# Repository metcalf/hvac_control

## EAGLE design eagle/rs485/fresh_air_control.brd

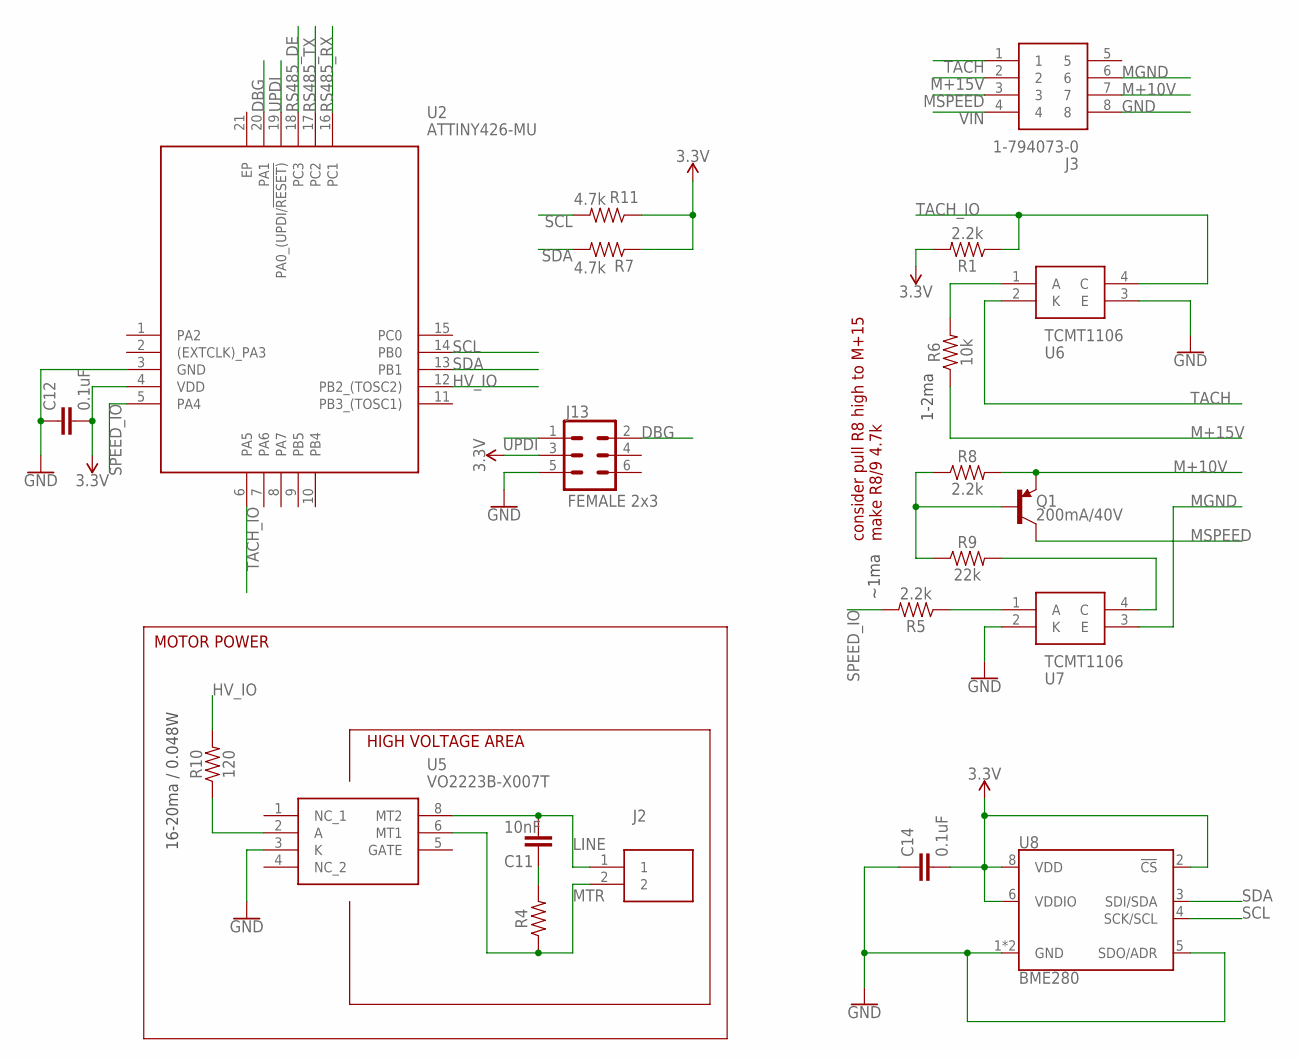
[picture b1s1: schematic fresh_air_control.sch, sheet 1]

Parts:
C11: 10nF; 0805
C12, C14: 0.1uF; 0603
J2: 1-770166-0; 17701660
J3: 1-794073-0; 17940730
J13: FEMALE 2x3; 2X3
Q1: 200mA/40V; SOT23-3
R1, R5, R8: 2.2k; 0603
R4: 100; 0805
R6: 10k; 0603
R7, R11: 4.7k; 0603
R9: 22k; 0603
R10: 120; 0603
U2: ATTINY426-MU; QFN40P300X300X90-21N
U5: VO2223B-X007T; VO2223BX007T
U6, U7: TCMT1106; SOIC127P700X230-4N
U8: BME280; LGA-8-2.5X2.5

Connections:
3.3V: C12.2, C14.2, J13.3, R1.2, R7.1, R11.1, U2.4 (VDD), U8.2 (!CS), U8.6 (VDDIO), U8.8 (VDD); also elsewhere on the board
DBG: J13.2, U2.20 (PA1)
GND: C12.1, C14.1, J3.8, J13.5, U2.3 (GND), U5.3 (K), U6.3 (E), U7.2 (K), U8.1 (GND), U8.5 (SDO/ADR), U8.7 (GND); also elsewhere on the board
HV_IO: R10.2, U2.12 (PB2_(TOSC2)); also elsewhere on the board
HV_SW: R10.1, U5.2 (A)
LINE: C11.1, J2.1, U5.8 (MT2)
M+10V: J3.7, Q1.2 (E), R8.2
M+15V: J3.2, R6.1
MGND: J3.6, U7.3 (E)
MSPEED: J3.3, Q1.3 (C)
MTR: J2.2, R4.1, U5.6 (MT1)
unnamed: R6.2, U6.1 (A)
unnamed: C11.2, R4.2
unnamed: R5.1, U7.1 (A)
unnamed: Q1.1 (B), R8.1, R9.1
unnamed: R9.2, U7.4 (C)
RS485_DE: U2.18 (PC3); also elsewhere on the board
RS485_RX: U2.16 (PC1); also elsewhere on the board
RS485_TX: U2.17 (PC2); also elsewhere on the board
SCL: R11.2, U2.14 (PB0), U8.4 (SCK/SCL); also elsewhere on the board
SDA: R7.2, U2.13 (PB1), U8.3 (SDI/SDA); also elsewhere on the board
SPEED_IO: R5.2, U2.5 (PA4); also elsewhere on the board
TACH: J3.1, U6.2 (K)
TACH_IO: R1.1, U2.6 (PA5), U6.4 (C); also elsewhere on the board
UPDI: J13.1, U2.19 (PA0_(UPDI/!RESET))
VIN: J3.4; also elsewhere on the board

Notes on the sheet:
HIGH VOLTAGE AREA
16-20ma / 0.048W
~1ma
1-2ma
MOTOR POWER
consider pull R8 high to M+15 make R8/9 4.7k

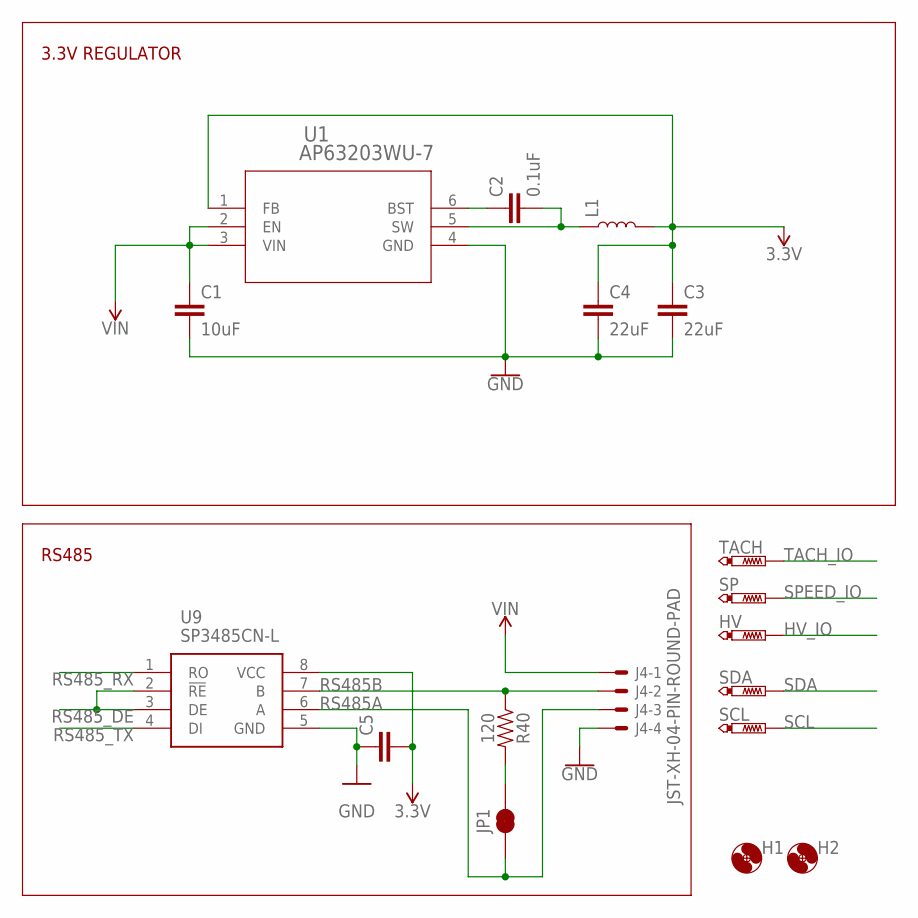
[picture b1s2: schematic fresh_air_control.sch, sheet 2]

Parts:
C1: 10uF; 1206
C2, C5: 0.1uF; 0603
C3, C4: 22uF; 0805
H1, H2: MOUNT-HOLE3.3; 3,3
HV: PTR1B1,27; B1,27
J4: JST-XH-04-PIN-ROUND-PAD; JST-XH-04-PACKAGE-ROUND-PAD
JP1: JUMPER-SMT_2_NC_TRACE_NO-SILK; SMT-JUMPER_2_NC_TRACE_NO-SILK
L1: 4.7μH_SHIELDED_INDUCTOR; 1008(2520)
R40: 120; 0603
SCL: PTR1B1,27; B1,27
SDA: PTR1B1,27; B1,27
SP: PTR1B1,27; B1,27
TACH: PTR1B1,27; B1,27
U1: AP63203WU-7; SOIC_05WU-7_DIO
U9: SP3485CN-L; SOIC127P600X175-8N

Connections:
3.3V: C3.1, C4.1, C5.2, L1.2, U1.1 (FB), U9.8 (VCC); also elsewhere on the board
GND: C1.2, C3.2, C4.2, C5.1, J4.4, U1.4 (GND), U9.5 (GND); also elsewhere on the board
HV_IO: HV.TP; also elsewhere on the board
unnamed: C2.2, L1.1, U1.5 (SW)
unnamed: C2.1, U1.6 (BST)
unnamed: JP1.2, R40.2
RS485A: J4.3, JP1.1, U9.6 (A)
RS485B: J4.2, R40.1, U9.7 (B)
RS485_DE: U9.2 (!RE), U9.3 (DE); also elsewhere on the board
RS485_RX: U9.1 (RO); also elsewhere on the board
RS485_TX: U9.4 (DI); also elsewhere on the board
SCL: SCL.TP; also elsewhere on the board
SDA: SDA.TP; also elsewhere on the board
SPEED_IO: SP.TP; also elsewhere on the board
TACH_IO: TACH.TP; also elsewhere on the board
VIN: C1.1, J4.1, U1.2 (EN), U1.3 (VIN); also elsewhere on the board

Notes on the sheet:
3.3V REGULATOR
RS485

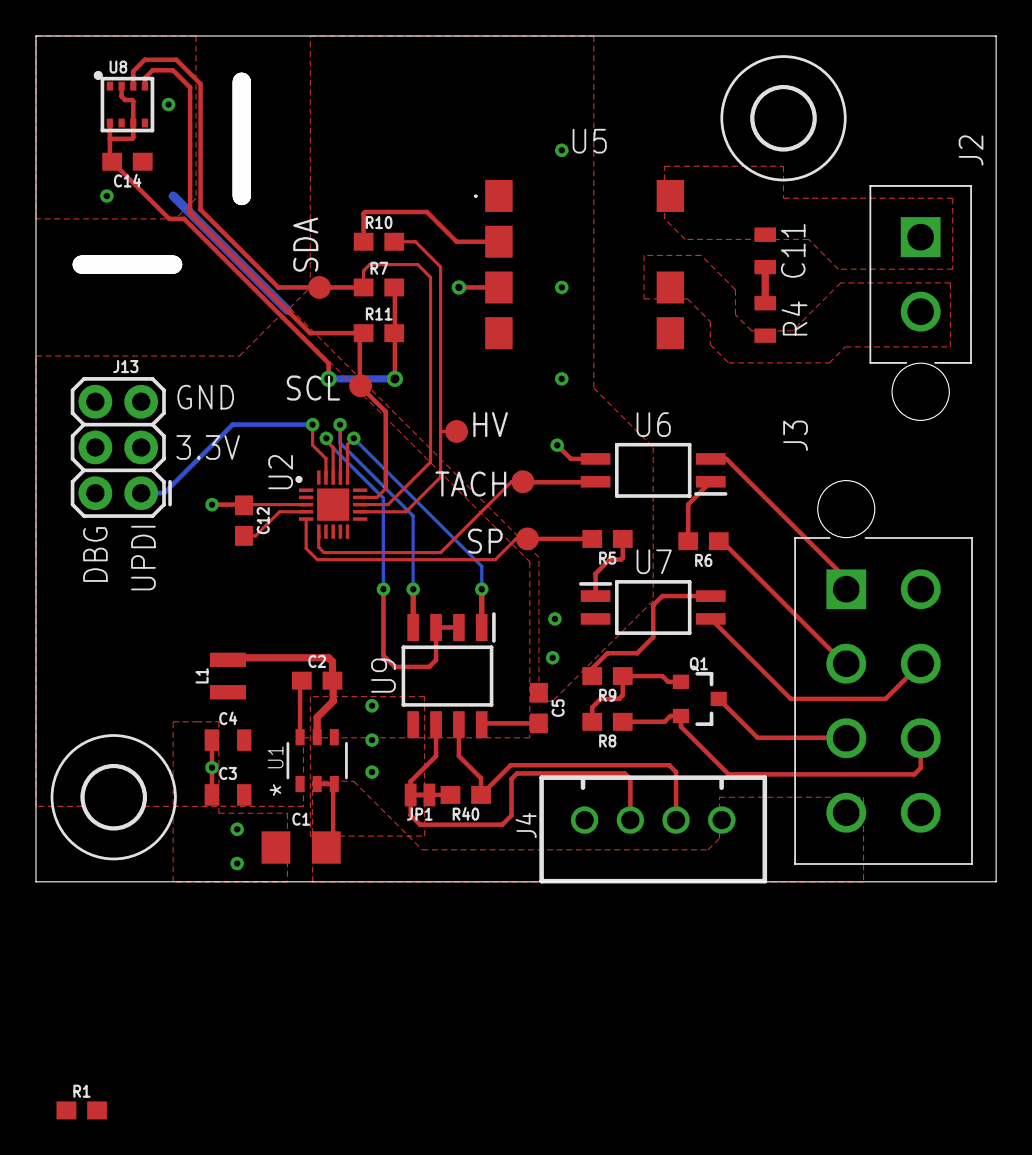
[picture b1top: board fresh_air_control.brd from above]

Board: 2 copper layers, 53.3 x 47.0 mm, 39 parts (0 on the bottom side), 31 nets.

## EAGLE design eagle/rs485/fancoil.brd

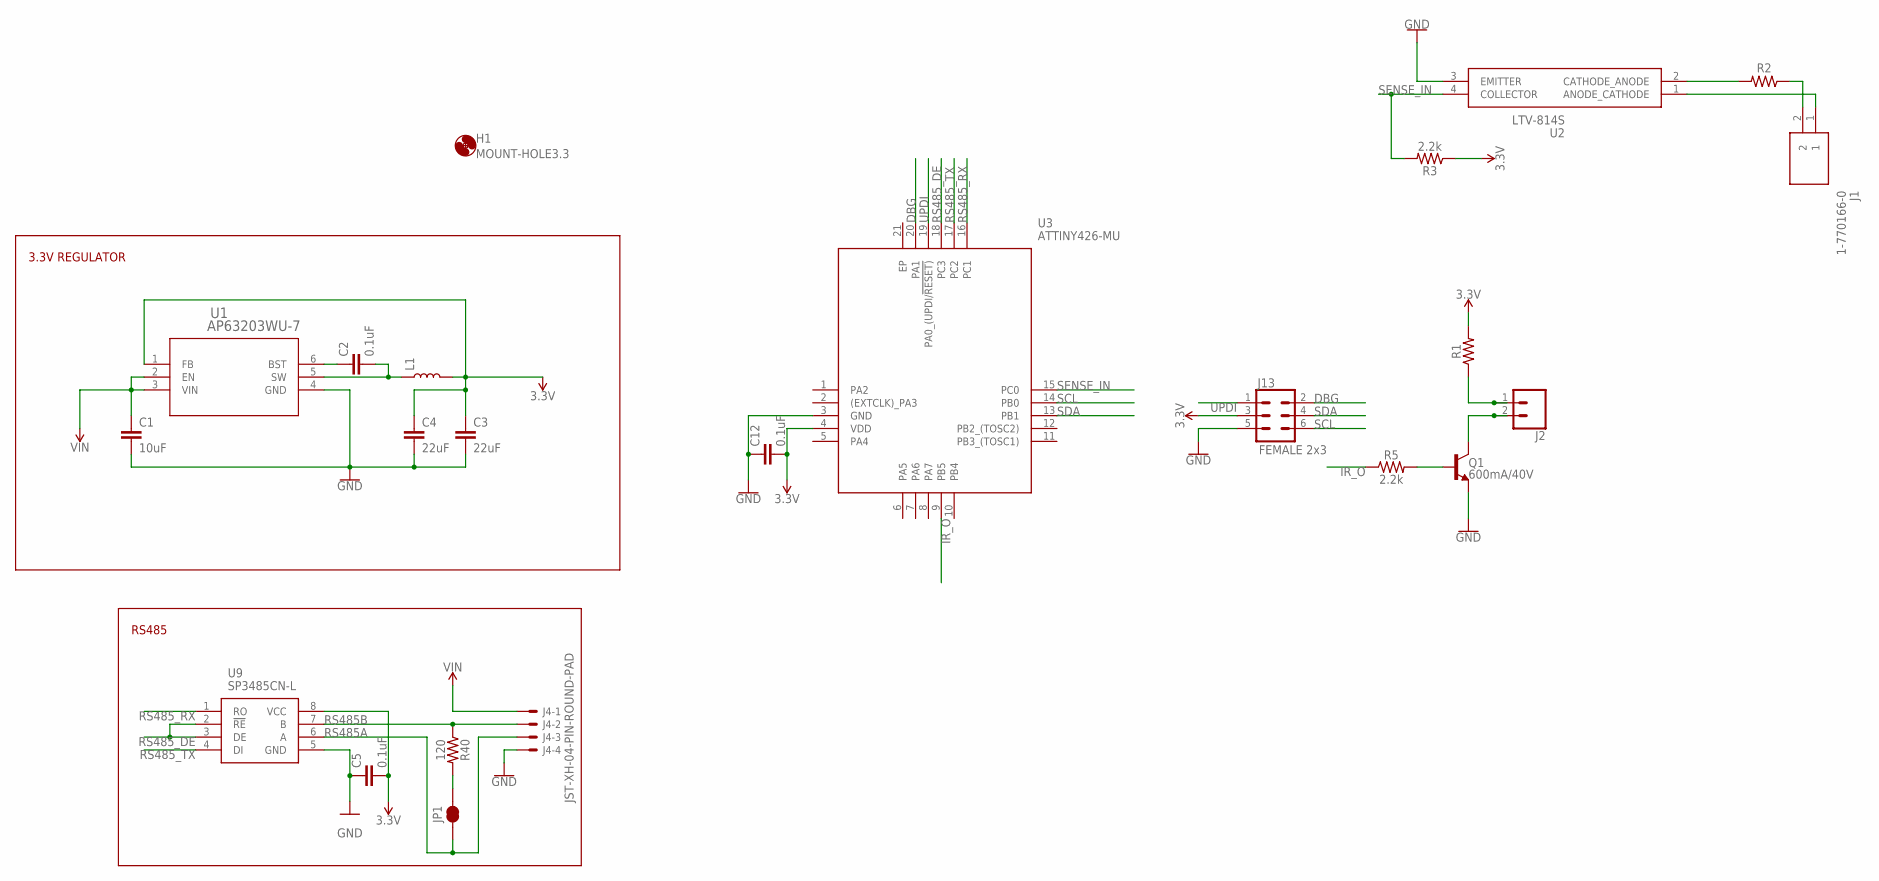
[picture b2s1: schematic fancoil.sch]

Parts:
C1: 10uF; 1206
C2, C5, C12: 0.1uF; 0603
C3, C4: 22uF; 0805
H1: MOUNT-HOLE3.3; 3,3
J1: 1-770166-0; 17701660
J2: CONN_02; 1X02
J4: JST-XH-04-PIN-ROUND-PAD; JST-XH-04-PACKAGE-ROUND-PAD
J13: FEMALE 2x3; 2X3
JP1: JUMPER-SMT_2_NC_TRACE_NO-SILK; SMT-JUMPER_2_NC_TRACE_NO-SILK
L1: 4.7μH_SHIELDED_INDUCTOR; 1008(2520)
Q1: 600mA/40V; SOT23-3
R1: 68OHM-0603-1/10W-1%; 0603
R2: AXIAL-0.3
R3, R5: 2.2k; 0603
R40: 120; 0603
U1: AP63203WU-7; SOIC_05WU-7_DIO
U2: LTV-814S; SOP254P1016X460-4N
U3: ATTINY426-MU; QFN40P300X300X90-21N
U9: SP3485CN-L; SOIC127P600X175-8N

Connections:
3.3V: C3.1, C4.1, C5.2, C12.2, J13.3, L1.2, R1.2, R3.1, U1.1 (FB), U3.4 (VDD), U9.8 (VCC)
DBG: J13.2, U3.20 (PA1)
GND: C1.2, C3.2, C4.2, C5.1, C12.1, J4.4, J13.5, Q1.2 (E), U1.4 (GND), U2.3 (EMITTER), U3.3 (GND), U9.5 (GND)
IR_O: R5.1, U3.9 (PB5)
unnamed: C2.2, L1.1, U1.5 (SW)
unnamed: C2.1, U1.6 (BST)
unnamed: JP1.2, R40.2
unnamed: J2.1, R1.1
unnamed: Q1.1 (B), R5.2
unnamed: J1.2, R2.P$1 (1)
unnamed: J1.1, U2.1 (ANODE_CATHODE)
unnamed: R2.P$2 (2), U2.2 (CATHODE_ANODE)
unnamed: J2.2, Q1.3 (C)
RS485A: J4.3, JP1.1, U9.6 (A)
RS485B: J4.2, R40.1, U9.7 (B)
RS485_DE: U3.18 (PC3), U9.2 (!RE), U9.3 (DE)
RS485_RX: U3.16 (PC1), U9.1 (RO)
RS485_TX: U3.17 (PC2), U9.4 (DI)
SCL: J13.6, U3.14 (PB0)
SDA: J13.4, U3.13 (PB1)
SENSE_IN: R3.2, U2.4 (COLLECTOR), U3.15 (PC0)
UPDI: J13.1, U3.19 (PA0_(UPDI/!RESET))
VIN: C1.1, J4.1, U1.2 (EN), U1.3 (VIN)

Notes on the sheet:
3.3V REGULATOR
RS485

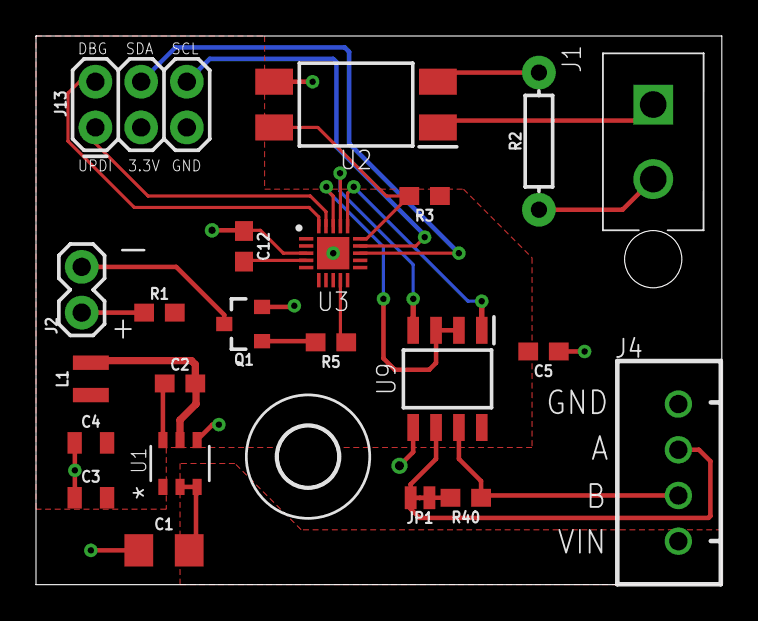
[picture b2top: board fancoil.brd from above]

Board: 2 copper layers, 38.1 x 30.5 mm, 23 parts (0 on the bottom side), 23 nets.

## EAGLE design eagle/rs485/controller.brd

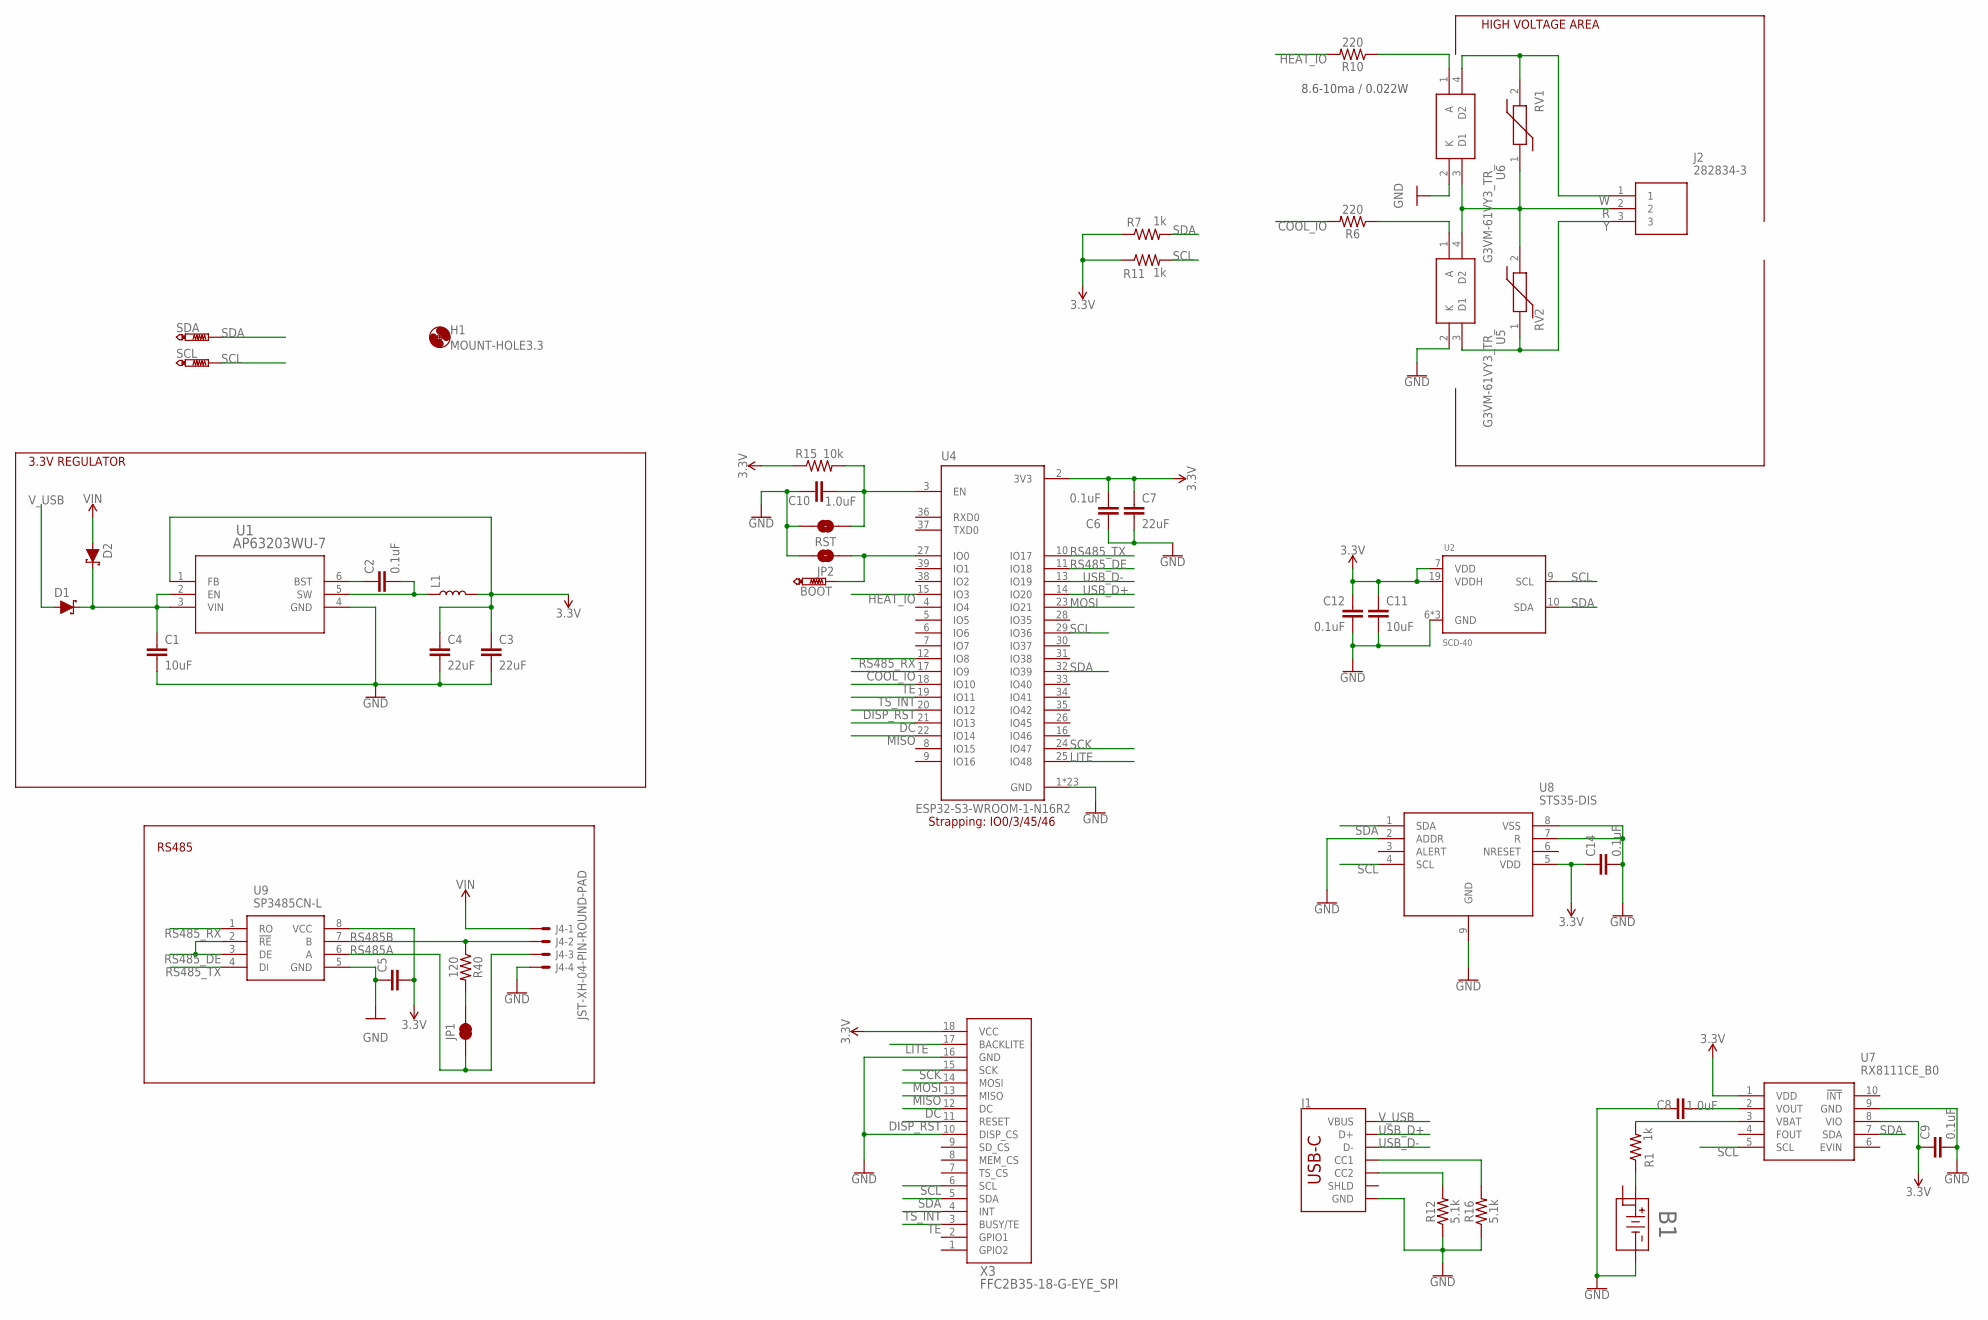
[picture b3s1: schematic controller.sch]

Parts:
B1: BAT-HLD-012-SMT; BAT-HLD-012-SMT_TEC
BOOT: PTR1B1,27; B1,27
C1, C11: 10uF; 1206
C2, C5, C6, C9, C12, C14: 0.1uF; 0603
C3, C4, C7: 22uF; 0805
C8, C10: 1.0uF; 0603
D1, D2: 1A/23V/620mV; SOD-323
H1: MOUNT-HOLE3.3; 3,3
J1: USB_C_2-LAYER_PADS; USB-C-16P-2LAYER-PADS
J2: 282834-3; 2828343
J4: JST-XH-04-PIN-ROUND-PAD; JST-XH-04-PACKAGE-ROUND-PAD
JP1: JUMPER-SMT_2_NC_TRACE_NO-SILK; SMT-JUMPER_2_NC_TRACE_NO-SILK
JP2: JUMPER-SMT_2_NO_NO-SILK; SMT-JUMPER_2_NO_NO-SILK
L1: 4.7μH_SHIELDED_INDUCTOR; 1008(2520)
R1, R7, R11: 1k; 0603
R6, R10: 220; 0603
R12, R16: 5.1k; 0603
R15: 10k; 0603
R40: 120; 0603
RST: JUMPER-SMT_2_NO_NO-SILK; SMT-JUMPER_2_NO_NO-SILK
RV1, RV2: ZV35K1210251NIR1; VARC3225X145N
SCL: PTR1B1,27; B1,27
SDA: PTR1B1,27; B1,27
U1: AP63203WU-7; SOIC_05WU-7_DIO
U2: SCD-40; SCD40
U4: ESP32-S3-WROOM-1-N16R2; XCVR_ESP32-S3-WROOM-1-N16R2
U5, U6: G3VM-61VY3_TR_; G3VM61VY3TR
U7: RX8111CE_B0; RX8111CEB0
U8: STS35-DIS; SON50P250X250X100-9N
U9: SP3485CN-L; SOIC127P600X175-8N
X3: FFC2B35-18-G-EYE_SPI; FFC2B3518G

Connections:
3.3V: C3.1, C4.1, C5.2, C6.2, C7.1, C9.1, C11.1, C12.2, C14.1, L1.2, R7.1, R11.1, R15.1, U1.1 (FB), U2.7 (VDD), U2.19 (VDDH), U4.2 (3V3), U7.1 (VDD), U7.8 (VIO), U8.5 (VDD), U9.8 (VCC), X3.18 (VCC)
COOL_IO: R6.2, U4.17 (IO9)
DC: U4.21 (IO13), X3.12 (DC)
DISP_RST: U4.20 (IO12), X3.11 (RESET)
GND: B1.3, C1.2, C3.2, C4.2, C5.1, C6.1, C7.2, C8.1, C9.2, C10.1, C11.2, C12.1, C14.2, J1.GND, J1.GND2 (GND), J4.4, JP2.2, R12.1, R16.1, RST.2, U1.4 (GND), U2.6 (GND), U2.20 (GND), U2.P$1 (GND), U4.1 (GND), U4.40 (GND), U4.41_1 (GND), U4.41_2 (GND), U4.41_3 (GND), U4.41_4 (GND), U4.41_5 (GND), U4.41_6 (GND), U4.41_7 (GND), U4.41_8 (GND), U4.41_9 (GND), U4.41_10 (GND), U4.41_11 (GND), U4.41_12 (GND), U4.41_13 (GND), U4.41_14 (GND), U4.41_15 (GND), U4.41_16 (GND), U4.41_17 (GND), U4.41_18 (GND), U4.41_19 (GND), U4.41_20 (GND), U4.41_21 (GND), U5.2 (K), U6.2 (K), U7.9 (GND), U8.2 (ADDR), U8.7 (R), U8.8 (VSS), U8.9 (GND), U9.5 (GND), X3.10 (DISP_CS), X3.16 (GND)
HEAT_IO: R10.2, U4.15 (IO3)
LITE: U4.25 (IO48), X3.17 (BACKLITE)
MISO: U4.22 (IO14), X3.13 (MISO)
MOSI: U4.23 (IO21), X3.14 (MOSI)
unnamed: C2.2, L1.1, U1.5 (SW)
unnamed: C2.1, U1.6 (BST)
unnamed: BOOT.TP, JP2.1, U4.27 (IO0)
unnamed: R6.1, U5.1 (A)
unnamed: JP1.2, R40.2
unnamed: B1.1, R1.1
unnamed: J1.A5 (CC1), R16.2
unnamed: C10.2, R15.2, RST.1, U4.3 (EN)
unnamed: R10.1, U6.1 (A)
unnamed: J1.B5 (CC2), R12.2
R: J2.2, RV1.1, RV2.2, U5.4 (D2), U6.3 (D1)
REG_IN: C1.1, D1.C, D2.C, U1.2 (EN), U1.3 (VIN)
RS485A: J4.3, JP1.1, U9.6 (A)
RS485B: J4.2, R40.1, U9.7 (B)
RS485_DE: U4.11 (IO18), U9.2 (!RE), U9.3 (DE)
RS485_RX: U4.12 (IO8), U9.1 (RO)
RS485_TX: U4.10 (IO17), U9.4 (DI)
RTC_VBAT: R1.2, U7.3 (VBAT)
RTC_VOUT: C8.2, U7.2 (VOUT)
SCK: U4.24 (IO47), X3.15 (SCK)
SCL: R11.2, SCL.TP, U2.9 (SCL), U4.29 (IO36), U7.5 (SCL), U8.4 (SCL), X3.6 (SCL)
SDA: R7.2, SDA.TP, U2.10 (SDA), U4.32 (IO39), U7.7 (SDA), U8.1 (SDA), X3.5 (SDA)
TE: U4.18 (IO10), X3.3 (BUSY/TE)
TS_INT: U4.19 (IO11), X3.4 (INT)
USB_D+: J1.A6 (D+), J1.B6 (D+), U4.14 (IO20)
USB_D-: J1.A7 (D-), J1.B7 (D-), U4.13 (IO19)
VIN: D2.A, J4.1
V_USB: D1.A, J1.VBUS1 (VBUS), J1.VBUS2 (VBUS)
W: J2.1, RV1.2, U6.4 (D2)
Y: J2.3, RV2.1, U5.3 (D1)

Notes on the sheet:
Strapping: IO0/3/45/46
HIGH VOLTAGE AREA
8.6-10ma / 0.022W
3.3V REGULATOR
RS485

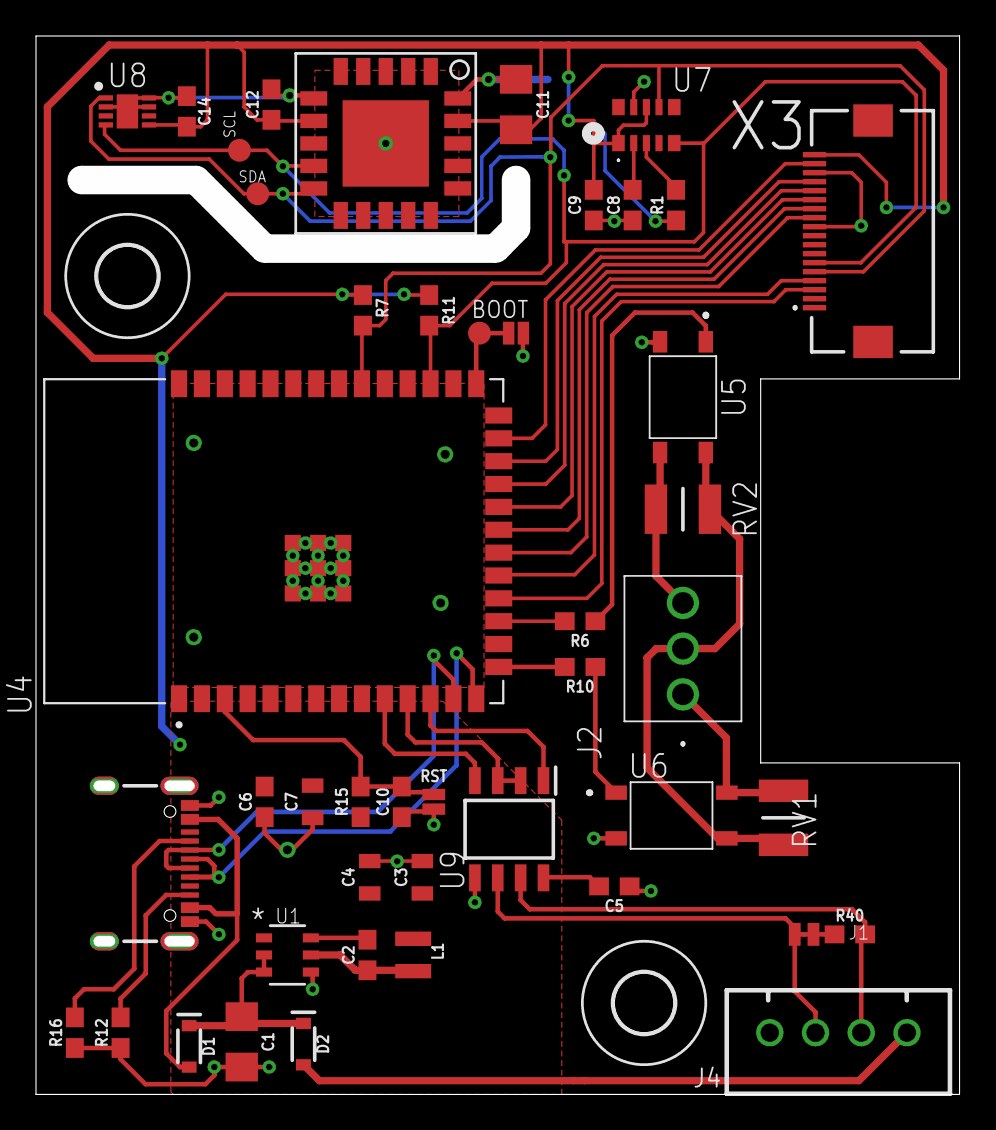
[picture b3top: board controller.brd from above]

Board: 2 copper layers, 51.3 x 58.8 mm, 48 parts (1 on the bottom side), 39 nets.

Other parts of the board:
H2: MOUNT-HOLE3.3; 3,3

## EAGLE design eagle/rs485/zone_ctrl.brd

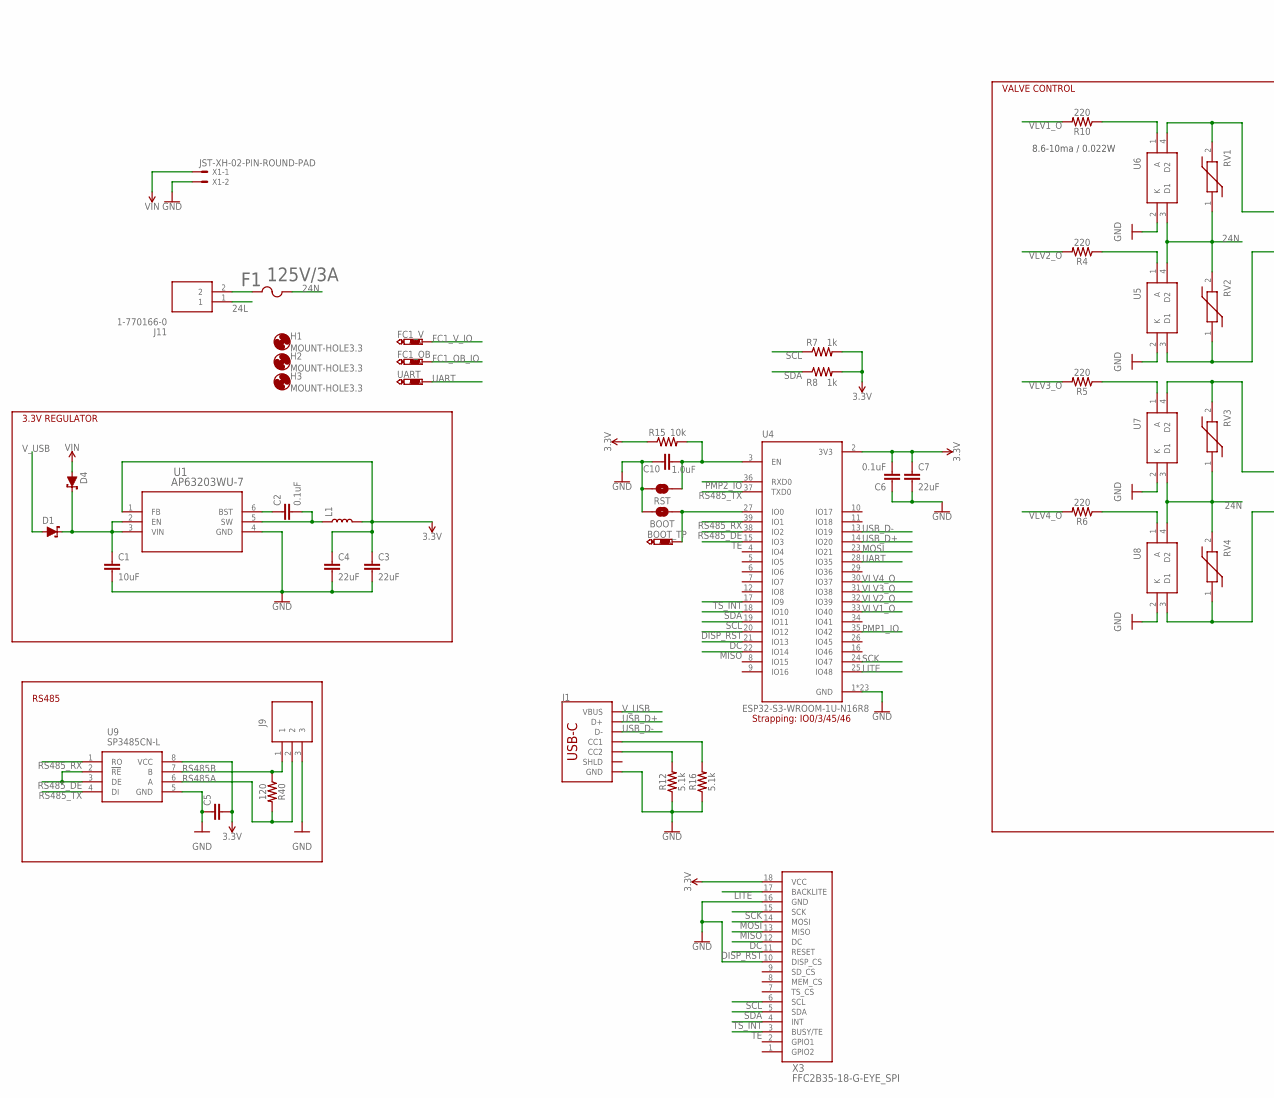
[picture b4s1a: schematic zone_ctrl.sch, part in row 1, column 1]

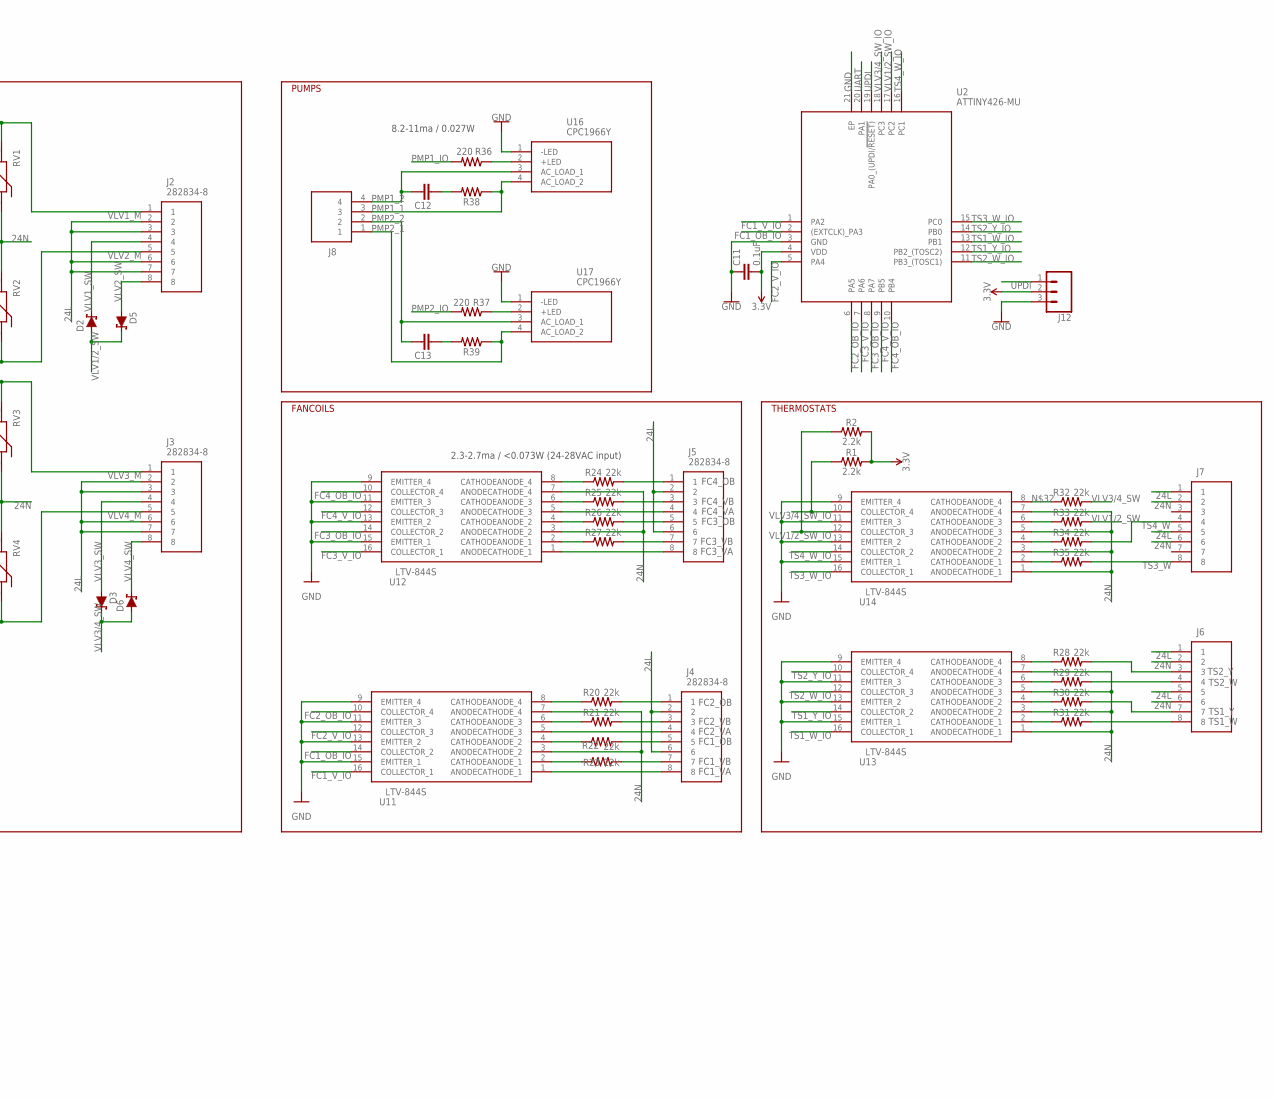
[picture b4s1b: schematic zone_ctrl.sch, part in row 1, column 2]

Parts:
BOOT: JUMPER-SMT_2_NO_NO-SILK; SMT-JUMPER_2_NO_NO-SILK
BOOT_TP: PTR1B1,27; B1,27
C1: 10uF; 1206
C2, C5, C6, C11: 0.1uF; 0603
C3, C4, C7: 22uF; 0805
C10: 1.0uF; 0603
C12, C13: 10nF; 0805
D1, D2, D3, D4, D5, D6: 1A/23V/620mV; SOD-323
F1: 125V/3A; 01550900M
FC1_OB, FC1_V: PTR1B1,27; B1,27
H1, H2, H3: MOUNT-HOLE3.3; 3,3
J1: USB_C_2-LAYER_PADS; USB-C-16P-2LAYER-PADS
J2, J3, J4, J5, J6, J7: 282834-8; 2828348
J8: 4DB-P108-04; SHDR4W132P0X826_1X4_3467X1270X
J9: 282834-3; 2828343
J11: 1-770166-0; 17701660
J12: 455-1750-1-ND; 1X03
L1: 4.7μH_SHIELDED_INDUCTOR; 1008(2520)
R1, R2: 2.2k; 0603
R4, R5, R6, R10, R36, R37: 220; 0603
R7, R8: 1k; 0603
R12, R16: 5.1k; 0603
R15: 10k; 0603
R20, R21, R22, R23, R24, R25, R26, R27, R28, R29, R30, R31, R32, R33, R34, R35: 22k; 0603
R38, R39: 100; 0805
R40: 120; 0603
RST: JUMPER-SMT_2_NO_NO-SILK; SMT-JUMPER_2_NO_NO-SILK
RV1, RV2, RV3, RV4: ZV35K1210251NIR1; VARC3225X145N
U1: AP63203WU-7; SOIC_05WU-7_DIO
U2: ATTINY426-MU; QFN40P300X300X90-21N
U4: ESP32-S3-WROOM-1U-N16R8; ESP32S3WROOM1UN16R8
U5, U6, U7, U8: G3VM-61VY3_TR_; G3VM61VY3TR
U9: SP3485CN-L; SOIC127P600X175-8N
U11, U12, U13, U14: LTV-844S; LTV846S
U16, U17: CPC1966Y
UART: PTR1B1,27; B1,27
X1: JST-XH-02-PIN-ROUND-PAD; JST-XH-02-PACKAGE-ROUND-PAD
X3: FFC2B35-18-G-EYE_SPI; FFC2B3518G

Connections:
3.3V: C3.1, C4.1, C5.2, C6.2, C7.1, C11.2, J12.2, L1.2, R1.2, R2.2, R7.2, R8.2, R15.1, U1.1 (FB), U2.4 (VDD), U4.2 (3V3), U9.8 (VCC), X3.18 (VCC)
24L: J2.2, J2.3, J2.6, J2.7, J3.2, J3.3, J3.6, J3.7, J4.2, J4.6, J5.2, J5.6, J6.1, J6.5, J7.1, J7.5, J11.1
24N: F1.2, J6.2, J6.6, J7.2, J7.6, RV1.1, RV2.2, RV3.1, RV4.2, U5.4 (D2), U6.3 (D1), U7.3 (D1), U8.4 (D2), U11.3 (ANODECATHODE_2), U11.7 (ANODECATHODE_4), U12.3 (ANODECATHODE_2), U12.7 (ANODECATHODE_4), U13.1 (ANODECATHODE_1), U13.3 (ANODECATHODE_2), U13.5 (ANODECATHODE_3), U13.7 (ANODECATHODE_4), U14.1 (ANODECATHODE_1), U14.3 (ANODECATHODE_2), U14.5 (ANODECATHODE_3), U14.7 (ANODECATHODE_4)
DC: U4.21 (IO13), X3.12 (DC)
DISP_RST: U4.20 (IO12), X3.11 (RESET)
FC1_OB: J4.5, R22.2
FC1_OB_IO: FC1_OB.TP, U2.2 ((EXTCLK)_PA3), U11.14 (COLLECTOR_2)
FC1_VA: J4.8, U11.1 (ANODECATHODE_1)
FC1_VB: J4.7, R23.2
FC1_V_IO: FC1_V.TP, U2.1 (PA2), U11.16 (COLLECTOR_1)
FC2_OB: J4.1, R20.2
FC2_OB_IO: U2.6 (PA5), U11.10 (COLLECTOR_4)
FC2_VA: J4.4, U11.5 (ANODECATHODE_3)
FC2_VB: J4.3, R21.2
FC2_V_IO: U2.5 (PA4), U11.12 (COLLECTOR_3)
FC3_OB: J5.5, R26.2
FC3_OB_IO: U2.8 (PA7), U12.14 (COLLECTOR_2)
FC3_VA: J5.8, U12.1 (ANODECATHODE_1)
FC3_VB: J5.7, R27.2
FC3_V_IO: U2.7 (PA6), U12.16 (COLLECTOR_1)
FC4_OB: J5.1, R24.2
FC4_OB_IO: U2.10 (PB4), U12.10 (COLLECTOR_4)
FC4_VA: J5.4, U12.5 (ANODECATHODE_3)
FC4_VB: J5.3, R25.2
FC4_V_IO: U2.9 (PB5), U12.12 (COLLECTOR_3)
GND: BOOT.2, C1.2, C3.2, C4.2, C5.1, C6.1, C7.2, C10.1, C11.1, J1.GND, J1.GND2 (GND), J9.3, J12.3, R12.1, R16.1, RST.2, U1.4 (GND), U2.3 (GND), U2.21 (EP), U4.1 (GND), U4.40 (GND), U4.41 (GND), U4.41_10 (GND), U4.41_11 (GND), U4.41_12 (GND), U4.41_13 (GND), U4.41_14 (GND), U4.41_15 (GND), U4.41_16 (GND), U4.41_17 (GND), U4.41_18 (GND), U4.41_19 (GND), U4.41_20 (GND), U4.41_21 (GND), U4.42 (GND), U4.43 (GND), U4.44 (GND), U4.45 (GND), U4.46 (GND), U4.47 (GND), U4.48 (GND), U4.49 (GND), U5.2 (K), U6.2 (K), U7.2 (K), U8.2 (K), U9.5 (GND), U11.9 (EMITTER_4), U11.11 (EMITTER_3), U11.13 (EMITTER_2), U11.15 (EMITTER_1), U12.9 (EMITTER_4), U12.11 (EMITTER_3), U12.13 (EMITTER_2), U12.15 (EMITTER_1), U13.9 (EMITTER_4), U13.11 (EMITTER_3), U13.13 (EMITTER_2), U13.15 (EMITTER_1), U14.9 (EMITTER_4), U14.11 (EMITTER_3), U14.13 (EMITTER_2), U14.15 (EMITTER_1), U16.1 (-LED), U17.1 (-LED), X1.2, X3.10 (DISP_CS), X3.16 (GND)
LITE: U4.25 (IO48), X3.17 (BACKLITE)
MISO: U4.22 (IO14), X3.13 (MISO)
MOSI: U4.23 (IO21), X3.14 (MOSI)
unnamed: C2.2, L1.1, U1.5 (SW)
unnamed: C2.1, U1.6 (BST)
unnamed: BOOT.1, BOOT_TP.TP, U4.27 (IO0)
unnamed: R20.1, U11.8 (CATHODEANODE_4)
unnamed: J1.A5 (CC1), R16.2
unnamed: C10.2, R15.2, RST.1, U4.3 (EN)
unnamed: R10.1, U6.1 (A)
unnamed: R4.1, U5.1 (A)
unnamed: R22.1, U11.4 (CATHODEANODE_2)
unnamed: R5.1, U7.1 (A)
unnamed: J1.B5 (CC2), R12.2
unnamed: R21.1, U11.6 (CATHODEANODE_3)
unnamed: R6.1, U8.1 (A)
unnamed: R23.1, U11.2 (CATHODEANODE_1)
unnamed: R24.1, U12.8 (CATHODEANODE_4)
unnamed: R25.1, U12.6 (CATHODEANODE_3)
unnamed: R26.1, U12.4 (CATHODEANODE_2)
unnamed: R27.1, U12.2 (CATHODEANODE_1)
unnamed: R28.1, U13.8 (CATHODEANODE_4)
unnamed: R29.1, U13.6 (CATHODEANODE_3)
unnamed: R30.1, U13.4 (CATHODEANODE_2)
unnamed: R31.1, U13.2 (CATHODEANODE_1)
unnamed: R35.1, U14.2 (CATHODEANODE_1)
unnamed: R34.1, U14.4 (CATHODEANODE_2)
unnamed: F1.1, J11.2
unnamed: R33.1, U14.6 (CATHODEANODE_3)
unnamed: R32.1, U14.8 (CATHODEANODE_4)
unnamed: R37.1, U17.2 (+LED)
unnamed: R36.1, U16.2 (+LED)
unnamed: C12.2, R38.2
unnamed: C13.2, R39.2
PMP1_1: J8.3, R38.1, U16.4 (AC_LOAD_2)
PMP1_2: C12.1, J8.4, U16.3 (AC_LOAD_1)
PMP1_IO: R36.2, U4.35 (IO42)
PMP2_1: J8.1, R39.1, U17.4 (AC_LOAD_2)
PMP2_2: C13.1, J8.2, U17.3 (AC_LOAD_1)
PMP2_IO: R37.2, U4.36 (RXD0)
REG_IN: C1.1, D1.C, D4.C, U1.2 (EN), U1.3 (VIN)
RS485A: J9.2, R40.2, U9.6 (A)
RS485B: J9.1, R40.1, U9.7 (B)
RS485_DE: U4.38 (IO2), U9.2 (!RE), U9.3 (DE)
RS485_RX: U4.39 (IO1), U9.1 (RO)
RS485_TX: U4.37 (TXD0), U9.4 (DI)
SCK: U4.24 (IO47), X3.15 (SCK)
SCL: R7.1, U4.19 (IO11), X3.6 (SCL)
SDA: R8.1, U4.18 (IO10), X3.5 (SDA)
TE: U4.15 (IO3), X3.3 (BUSY/TE)
TS1_W: J6.8, R31.2
TS1_W_IO: U2.13 (PB1), U13.16 (COLLECTOR_1)
TS1_Y: J6.7, R30.2
TS1_Y_IO: U2.12 (PB2_(TOSC2)), U13.14 (COLLECTOR_2)
TS2_W: J6.4, R29.2
TS2_W_IO: U2.11 (PB3_(TOSC1)), U13.12 (COLLECTOR_3)
TS2_Y: J6.3, R28.2
TS2_Y_IO: U2.14 (PB0), U13.10 (COLLECTOR_4)
TS3_W: J7.8, R35.2
TS3_W_IO: U2.15 (PC0), U14.16 (COLLECTOR_1)
TS4_W: J7.4, R34.2
TS4_W_IO: U2.16 (PC1), U14.14 (COLLECTOR_2)
TS_INT: U4.17 (IO9), X3.4 (INT)
UART: U2.20 (PA1), U4.28 (IO35), UART.TP
UPDI: J12.1, U2.19 (PA0_(UPDI/!RESET))
USB_D+: J1.A6 (D+), J1.B6 (D+), U4.14 (IO20)
USB_D-: J1.A7 (D-), J1.B7 (D-), U4.13 (IO19)
VIN: D4.A, X1.1
VLV1/2_SW: D2.A, D5.C, R33.2
VLV1/2_SW_IO: R2.1, U2.17 (PC2), U14.12 (COLLECTOR_3)
VLV1_M: J2.1, RV1.2, U6.4 (D2)
VLV1_O: R10.2, U4.33 (IO40)
VLV1_SW: D2.C, J2.4
VLV2_M: J2.5, RV2.1, U5.3 (D1)
VLV2_O: R4.2, U4.32 (IO39)
VLV2_SW: D5.A, J2.8
VLV3/4_SW: D3.C, D6.A, R32.2
VLV3/4_SW_IO: R1.1, U2.18 (PC3), U14.10 (COLLECTOR_4)
VLV3_M: J3.1, RV3.2, U7.4 (D2)
VLV3_O: R5.2, U4.31 (IO38)
VLV3_SW: D3.A, J3.4
VLV4_M: J3.5, RV4.1, U8.3 (D1)
VLV4_O: R6.2, U4.30 (IO37)
VLV4_SW: D6.C, J3.8
V_USB: D1.A, J1.VBUS1 (VBUS), J1.VBUS2 (VBUS)

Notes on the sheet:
3.3V REGULATOR
Strapping: IO0/3/45/46
VALVE CONTROL
RS485
FANCOILS
THERMOSTATS
PUMPS
8.6-10ma / 0.022W
2.3-2.7ma / <0.073W (24-28VAC input)
8.2-11ma / 0.027W

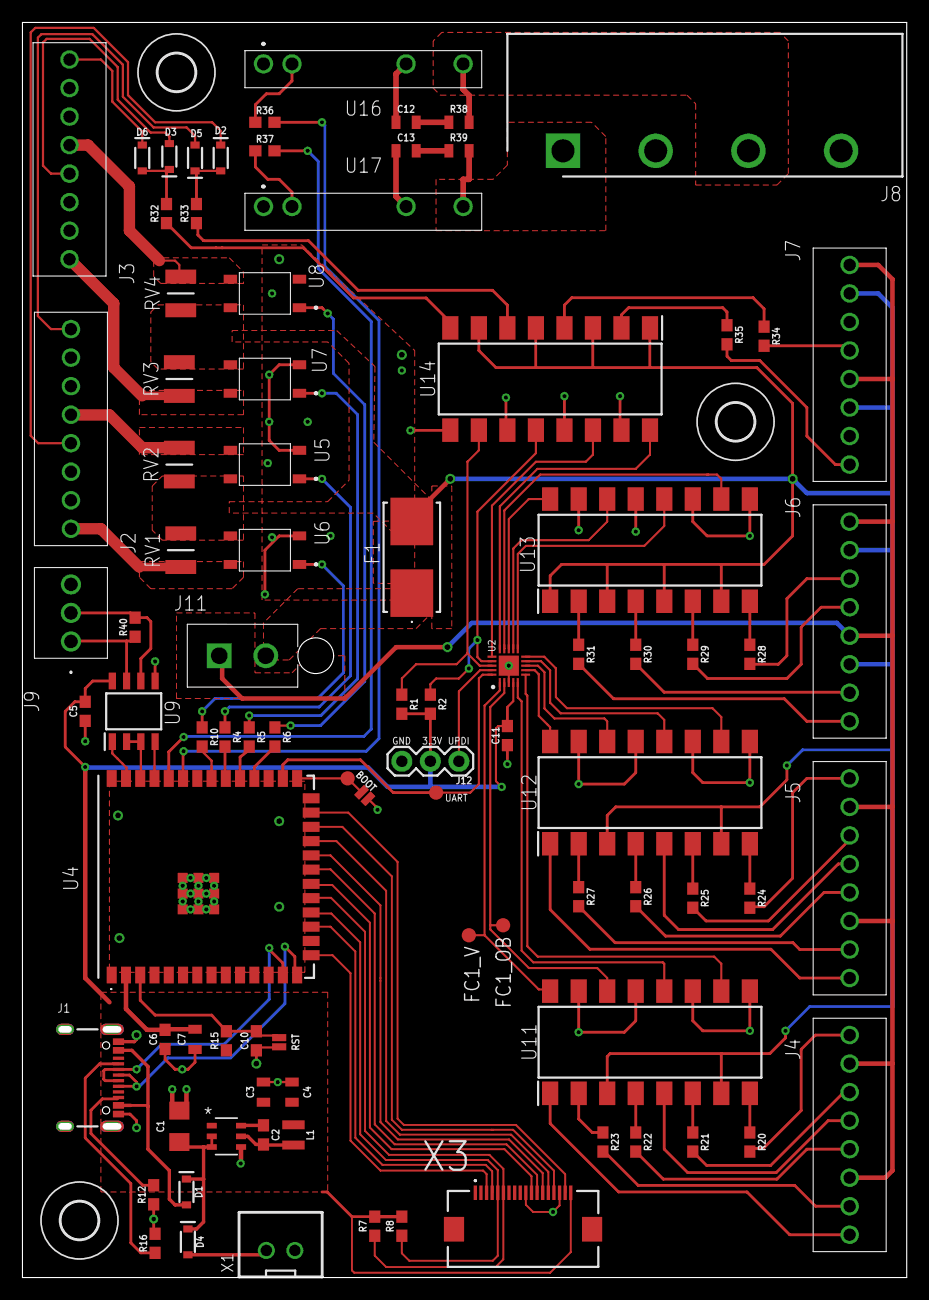
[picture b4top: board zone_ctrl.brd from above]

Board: 2 copper layers, 78.7 x 111.8 mm, 91 parts (0 on the bottom side), 111 nets.

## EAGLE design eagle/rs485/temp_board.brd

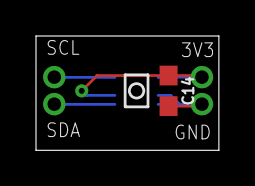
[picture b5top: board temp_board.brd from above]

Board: 2 copper layers, 10.2 x 6.3 mm, 4 parts (1 on the bottom side), 4 nets.

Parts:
C14: 0.1uF; 0603
J1, J2: 1X02_1.5MM_NO_SILK
U8: STS35-DIS; SON50P250X250X100-9N

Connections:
3.3V: C14.1, J1.2, U8.2, U8.5
GND: C14.2, J1.1, U8.7, U8.8, U8.9
SCL: J2.2, U8.4
SDA: J2.1, U8.1

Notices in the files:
parts and their libraries:
SparkFun-Capacitors: Licensing: Creative Commons ShareAlike 4.0 International - https://creativecommons.org/licenses/by-sa/4.0
COPYRIGHT: Copyright (C) 2023 Ultra Librarian. All rights reserved.
COPYRIGHT: Copyright (C) 2024 Ultra Librarian. All rights reserved.
